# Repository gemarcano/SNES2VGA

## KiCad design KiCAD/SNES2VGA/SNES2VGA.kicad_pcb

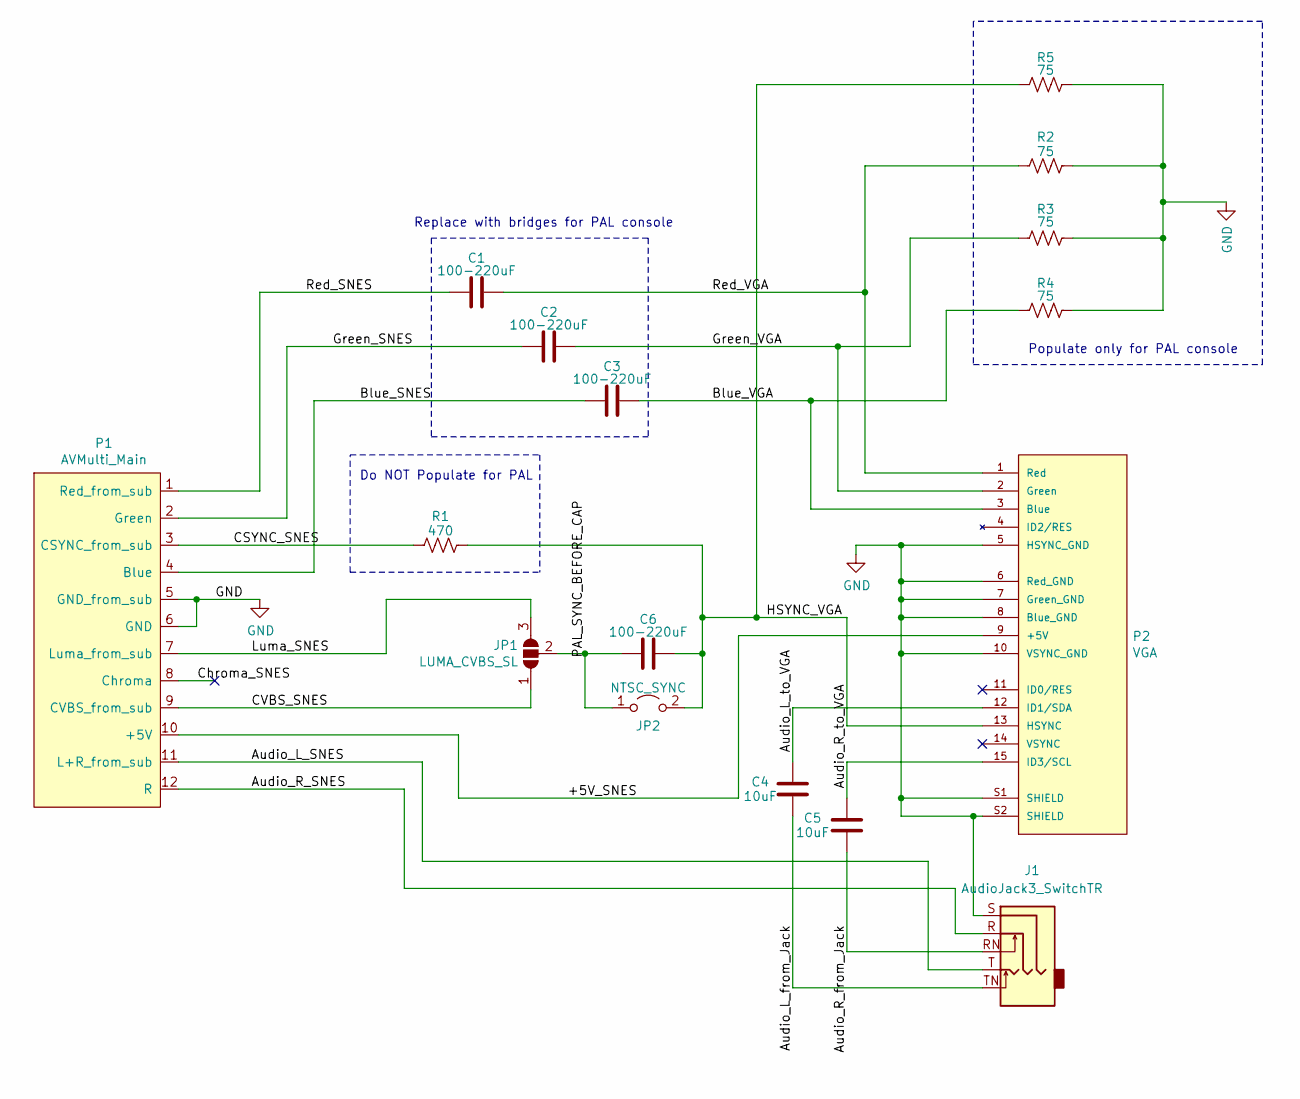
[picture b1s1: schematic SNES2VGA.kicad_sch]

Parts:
C1, C2, C3, C6: 100-220uF; C_1206_3216Metric
C4, C5: 10uF; C_0603_1608Metric
J1: AudioJack3_SwitchTR; Jack_3.5mm_CUI_SJ1-3535NG_Horizontal
JP1: LUMA_CVBS_SL; SolderJumper-3_P1.3mm_Open_RoundedPad1.0x1.5mm
JP2: NTSC_SYNC; SolderJumper-2_P1.3mm_Open_RoundedPad1.0x1.5mm
P1: AVMulti_Main; AV_Multi_Main
P2: VGA; VGA_female_rightangle_slim; PARTREV N/A
R1: 470; R_0603_1608Metric
R2, R3, R4, R5: 75; R_0603_1608Metric

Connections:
/+5V_SNES: P1.10 (+5V), P2.9 (+5V)
/Audio_L_SNES: J1.T, P1.11 (L+R_from_sub)
/Audio_L_from_Jack: C4.2, J1.TN
/Audio_L_to_VGA: C4.1, P2.12 (ID1/SDA)
/Audio_R_SNES: J1.R, P1.12 (R)
/Audio_R_from_Jack: C5.2, J1.RN
/Audio_R_to_VGA: C5.1, P2.15 (ID3/SCL)
/Blue_SNES: C3.1, P1.4 (Blue)
/Blue_VGA: C3.2, P2.3 (Blue), R4.1
/CSYNC_SNES: P1.3 (CSYNC_from_sub), R1.1
/CVBS_SNES: JP1.1 (A), P1.9 (CVBS_from_sub)
/Chroma_SNES: P1.8 (Chroma)
/Green_SNES: C2.1, P1.2 (Green)
/Green_VGA: C2.2, P2.2 (Green), R3.1
/HSYNC_VGA: C6.2, JP2.2 (B), P2.13 (HSYNC), R1.2, R5.1
/Luma_SNES: JP1.3 (B), P1.7 (Luma_from_sub)
/PAL_SYNC_BEFORE_CAP: C6.1, JP1.2 (C), JP2.1 (A)
/Red_SNES: C1.1, P1.1 (Red_from_sub)
/Red_VGA: C1.2, P2.1 (Red), R2.1
GND: J1.S, P1.5 (GND_from_sub), P1.6 (GND), P2.5 (HSYNC_GND), P2.6 (Red_GND), P2.7 (Green_GND), P2.8 (Blue_GND), P2.10 (VSYNC_GND), P2.S1 (SHIELD), P2.S2 (SHIELD), R2.2, R3.2, R4.2, R5.2

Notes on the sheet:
Do NOT Populate for PAL
Replace with bridges for PAL console
Populate only for PAL console

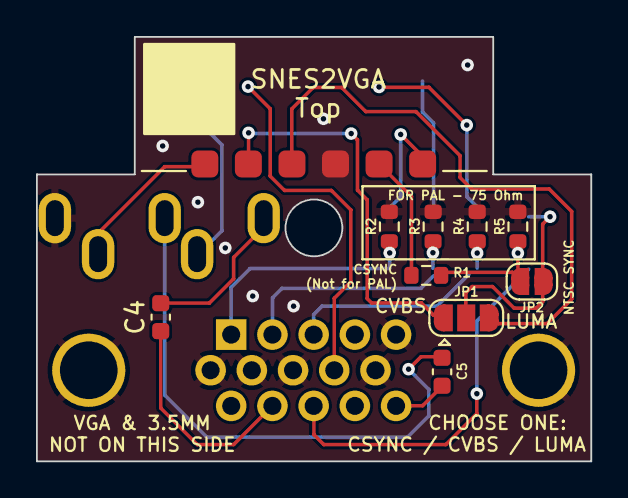
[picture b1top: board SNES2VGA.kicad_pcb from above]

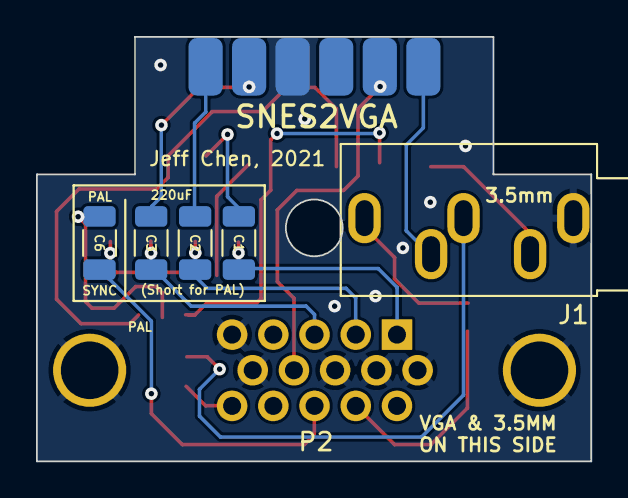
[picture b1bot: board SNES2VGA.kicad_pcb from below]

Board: 2 copper layers, 30.8 x 23.6 mm, 16 parts (6 on the bottom side), 19 nets.

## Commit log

2025-03-27 Update to KiCad 9
    - Use kicad symbols and footprints if possible
    - Add JLCPCB QR/number placement square/text
2025-03-28 Add part information for Digikey and Mfg#
